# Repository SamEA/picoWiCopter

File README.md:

picoWiCopter
============

A small Quadcopter for multi robot cooperation

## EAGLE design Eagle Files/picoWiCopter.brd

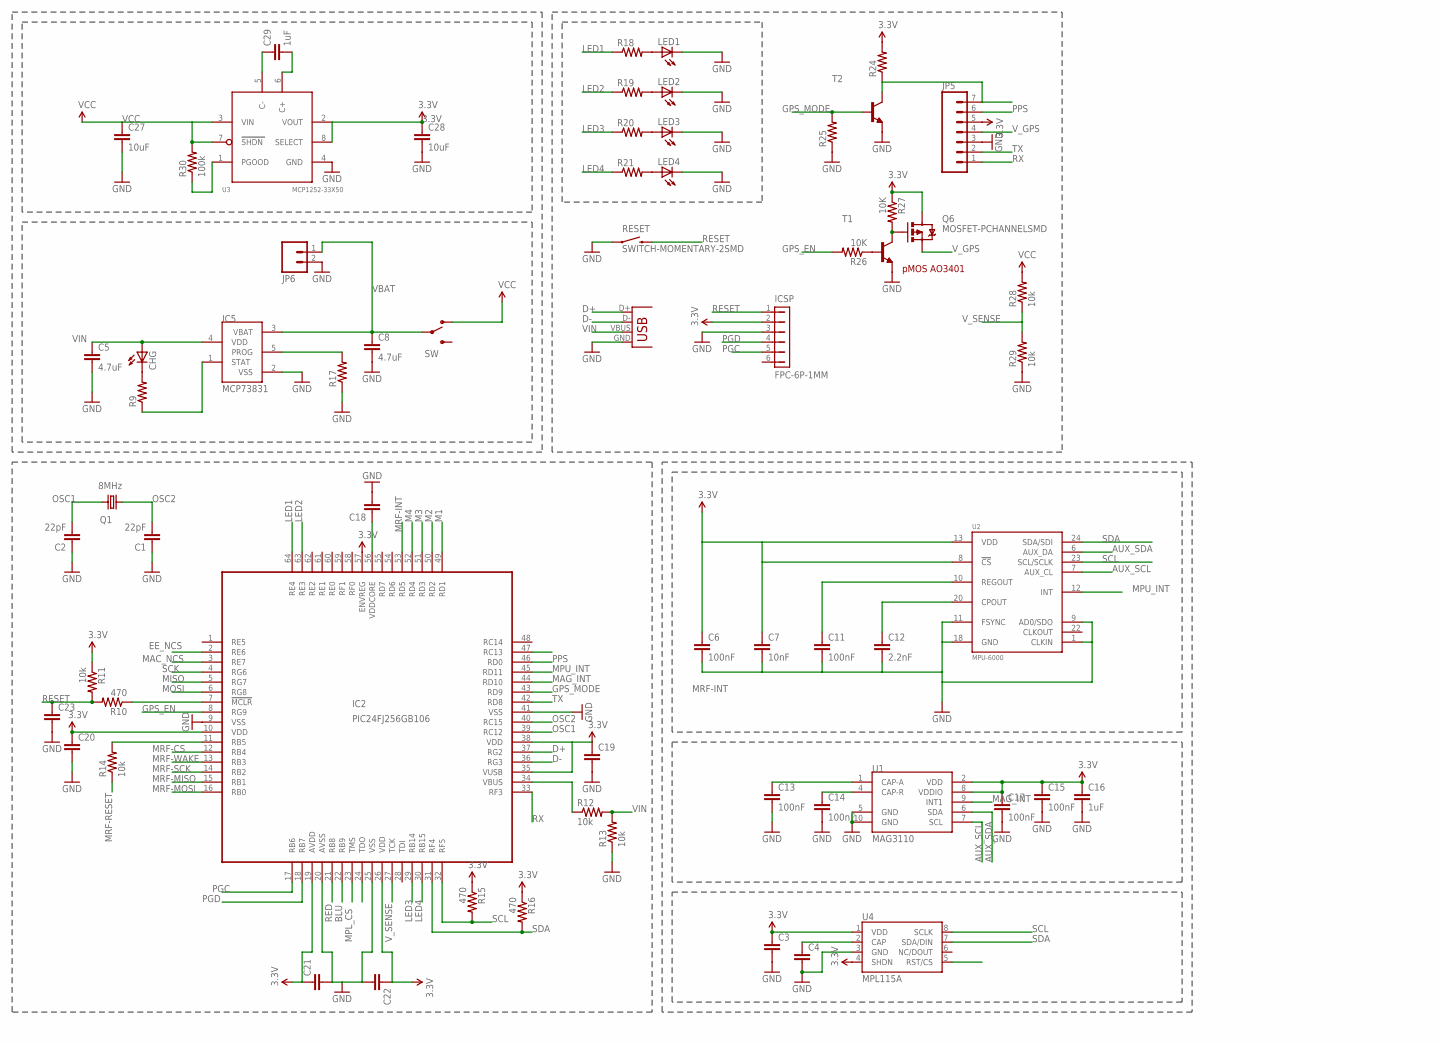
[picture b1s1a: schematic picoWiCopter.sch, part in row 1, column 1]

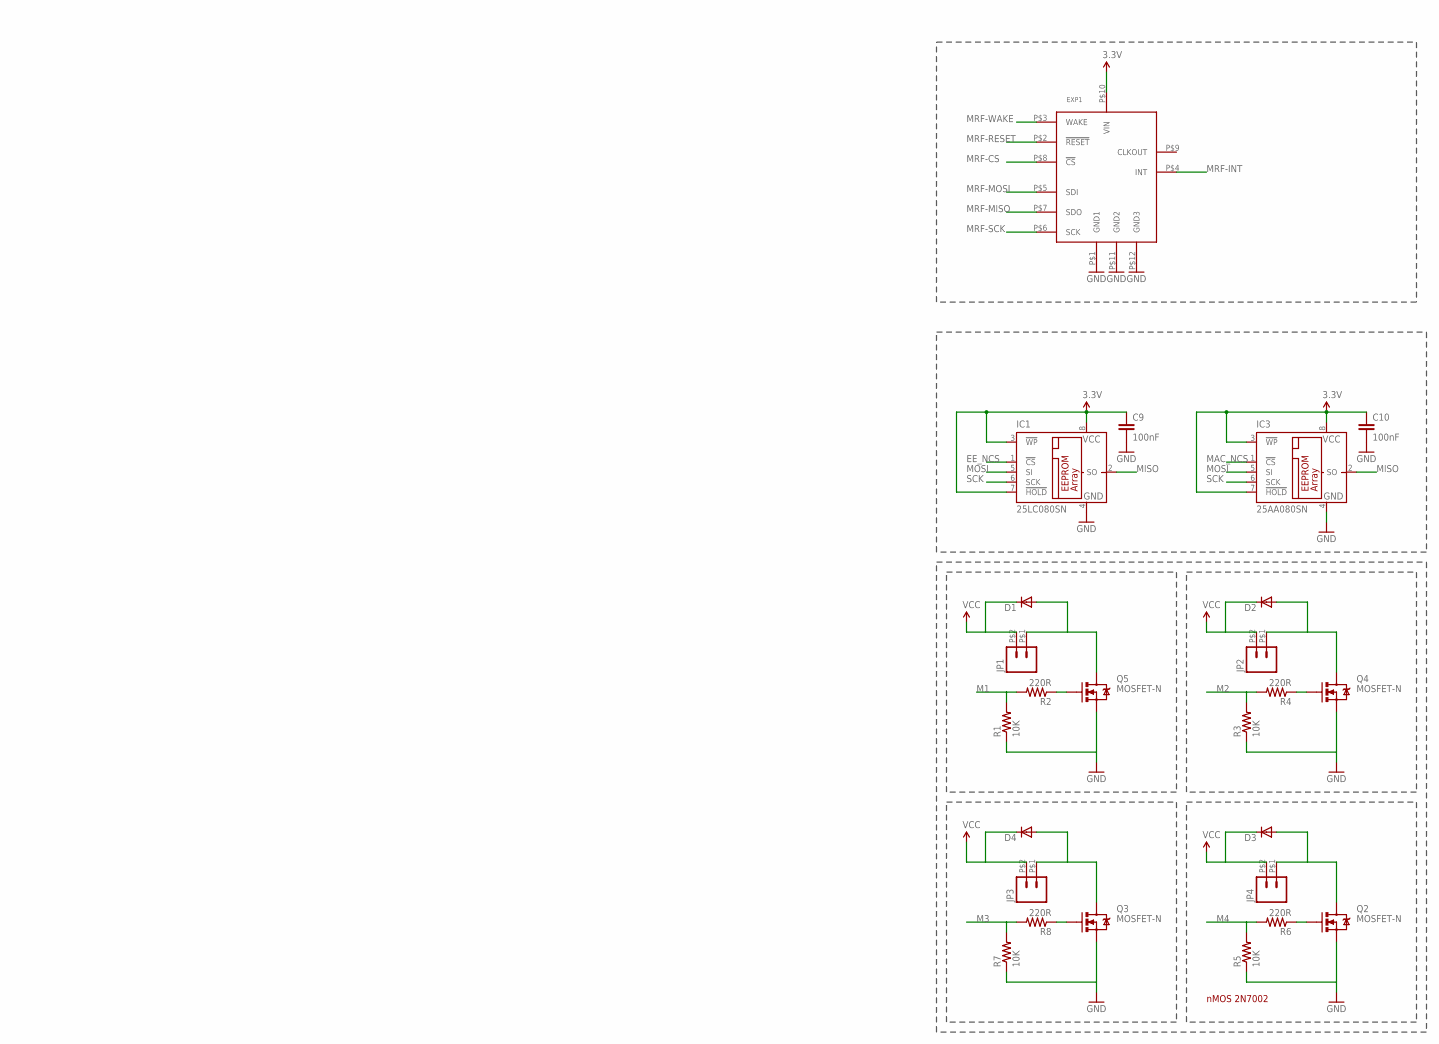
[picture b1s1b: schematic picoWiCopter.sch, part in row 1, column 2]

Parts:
C1, C2: 22pF; 0603-CAP
C3, C4, C19, C20, C21, C22, C23: CAP0603-CAP; 0603-CAP
C5, C8: 4.7uF; C1206
C6, C9, C10, C11, C13, C14, C15, C17: 100nF; 0603-CAP
C7: 10nF; 0603-CAP
C12: 2.2nF; 0603-CAP
C16, C29: 1uF; 0603-CAP
C18: CAP1206; 1206
C27, C28: 10uF; 1206
CHG: LEDCHIP-LED0603; CHIP-LED0603
D1, D2, D3, D4: DIODE-MINIMELF; MINIMELF
EXP1: MRF24J40MA"; MRF24J40MA
IC1: 25LC080SN; SO-08
IC2: PIC24FJ256GB106; TQFP64-10X10
IC3: 25AA080SN; SO-08
IC5: MCP73831; SOT23-5L
ICSP: FPC-6P-1MM
JP1, JP2, JP3, JP4: M02; 1X2SMD
JP5: M07; 1X07
JP6: M02PTH; 1X02
LED1, LED2, LED3, LED4: LED0603; LED-0603
Q1: 8MHz; CTS406
Q2, Q3, Q4, Q5: MOSFET-N; SOT23-3
Q6: MOSFET-PCHANNELSMD; SOT23-3
R1, R3, R5, R7, R26, R27: 10K; R0603
R2, R4, R6, R8: 220R; R0603
R9, R17, R18, R19, R20, R21, R24, R25: RESISTOR0603-RES; 0603-RES
R10, R15, R16: 470; 0603-RES
R11, R12, R13, R14, R28, R29: 10k; 0603-RES
R30: 100k; 0603-RES
RESET: SWITCH-MOMENTARY-2SMD; TACTILE_SWITCH_SMD
SW: SWITCH-SPDTPTH_LOCK; SWITCH-SPDT_LOCK.007S
T1, T2: BFR92-NPN-SOT23-BEC; SOT23-BEC
U1: MAG3110; DFN-10
U2: MPU-6000; QFN-24
U3: MCP1252-33X50; MSOP8
U4: MPL115A; LGA8
X3: USBSMD; USB-MINIB

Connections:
3.3V: C3.1, C6.1, C7.1, C9.1, C10.1, C15.1, C16.1, C17.1, C19.1, C20.1, C21.1, C22.1, C28.1, EXP1.P$10 (VIN), IC1.3 (!WP), IC1.7 (!HOLD), IC1.8 (VCC), IC2.10 (VDD), IC2.19 (AVDD), IC2.26 (VDD), IC2.35 (VUSB), IC2.38 (VDD), IC2.57 (ENVREG), IC3.3 (!WP), IC3.7 (!HOLD), IC3.8 (VCC), ICSP.2, JP5.5, Q6.3 (D), R11.1, R15.1, R16.1, R24.2, R27.1, U1.2 (VDD), U1.8 (VDDIO), U2.8 (!CS), U2.13 (VDD), U3.2 (VOUT), U3.8 (SELECT), U4.1 (VDD), U4.4 (SHDN)
AUX_SCL: U1.7 (SCL), U2.7 (AUX_CL)
AUX_SDA: U1.6 (SDA), U2.6 (AUX_DA)
BLU: IC2.22 (RB9)
C+1: C29.2, U3.6 (C+)
C-1: C29.1, U3.5 (C-)
D+: IC2.37 (RG2), X3.D+
D-: IC2.36 (RG3), X3.D-
EE_NCS: IC1.1 (!CS), IC2.2 (RE6)
GND: C1.1, C2.1, C3.2, C4.2, C5.2, C6.2, C7.2, C8.2, C9.2, C10.2, C11.2, C12.2, C13.2, C14.2, C15.2, C16.2, C17.2, C18.2, C19.2, C20.2, C21.2, C22.2, C23.2, C27.2, C28.2, EXP1.P$1 (GND1), EXP1.P$11 (GND2), EXP1.P$12 (GND3), IC1.4 (GND), IC2.9 (VSS), IC2.20 (AVSS), IC2.25 (VSS), IC2.41 (VSS), IC3.4 (GND), IC5.2 (VSS), ICSP.3, JP5.3, JP6.2, LED1.C, LED2.C, LED3.C, LED4.C, Q2.2 (S), Q3.2 (S), Q4.2 (S), Q5.2 (S), R1.1, R3.1, R5.1, R7.1, R13.1, R17.1, R25.1, R29.1, RESET.1, T1.E, T2.E, U1.5 (GND), U1.10 (GND), U2.1 (CLKIN), U2.9 (AD0/SDO), U2.11 (FSYNC), U2.18 (GND), U3.4 (GND), U4.3 (GND), X3.GND
GPS_EN: IC2.8 (RG9), R26.2
GPS_MODE: IC2.43 (RD9), R25.2, T2.B
LED1: IC2.64 (RE4), R18.1
LED2: IC2.63 (RE3), R19.1
LED3: IC2.29 (RB14), R20.1
LED4: IC2.30 (RB15), R21.1
M1: IC2.49 (RD1), R1.2, R2.2
M2: IC2.50 (RD2), R3.2, R4.2
M3: IC2.51 (RD3), R7.2, R8.2
M4: IC2.52 (RD4), R5.2, R6.2
MAC_NCS: IC2.3 (RE7), IC3.1 (!CS)
MAG_INT: IC2.44 (RD10), U1.9 (INT1)
MISO: IC1.2 (SO), IC2.5 (RG7), IC3.2 (SO)
MOSI: IC1.5 (SI), IC2.6 (RG8), IC3.5 (SI)
MPL_CS: IC2.23 (TMS), U4.5 (RST/CS)
MPU_INT: IC2.45 (RD11), U2.12 (INT)
MRF-CS: EXP1.P$8 (!CS), IC2.12 (RB4)
MRF-INT: EXP1.P$4 (INT), IC2.53 (RD5)
MRF-MISO: EXP1.P$7 (SDO), IC2.15 (RB1)
MRF-MOSI: EXP1.P$5 (SDI), IC2.16 (RB0)
MRF-RESET: EXP1.P$2 (!RESET), R14.1
MRF-SCK: EXP1.P$6 (SCK), IC2.14 (RB2)
MRF-WAKE: EXP1.P$3 (WAKE), IC2.13 (RB3)
unnamed: IC5.1 (STAT), R9.1
unnamed: CHG.C, R9.2
unnamed: C13.1, U1.1 (CAP-A)
unnamed: C14.1, U1.4 (CAP-R)
unnamed: D1.A, JP1.P$1 (1), Q5.3 (D)
unnamed: LED1.A, R18.2
unnamed: C18.1, IC2.56 (VDDCORE)
unnamed: IC2.34 (VBUS), R12.1
unnamed: IC2.7 (!MCLR), R10.1
unnamed: IC2.11 (RB5), R14.2
unnamed: D2.A, JP2.P$1 (1), Q4.3 (D)
unnamed: C12.1, U2.20 (CPOUT)
unnamed: C11.1, U2.10 (REGOUT)
unnamed: LED2.A, R19.2
unnamed: LED3.A, R20.2
unnamed: D3.A, JP4.P$1 (1), Q2.3 (D)
unnamed: LED4.A, R21.2
unnamed: D4.A, JP3.P$1 (1), Q3.3 (D)
unnamed: IC5.5 (PROG), R17.2
unnamed: JP5.7, R24.1, T2.C
unnamed: Q6.1 (G), R27.2, T1.C
unnamed: R26.1, T1.B
unnamed: R30.1, U3.1 (PGOOD)
unnamed: C4.1, U4.2 (CAP)
unnamed: Q5.1 (G), R2.1
unnamed: Q4.1 (G), R4.1
unnamed: Q2.1 (G), R6.1
unnamed: Q3.1 (G), R8.1
OSC1: C2.2, IC2.39 (RC12), Q1.3 (2)
OSC2: C1.2, IC2.40 (RC15), Q1.1
PGC: IC2.17 (RB6), ICSP.5
PGD: IC2.18 (RB7), ICSP.4
PPS: IC2.46 (RD0), JP5.6
RED: IC2.21 (RB8)
RESET: C23.1, ICSP.1, R10.2, R11.2, RESET.3 (2)
RX: IC2.33 (RF3), JP5.1
SCK: IC1.6 (SCK), IC2.4 (RG6), IC3.6 (SCK)
SCL: IC2.32 (RF5), R15.2, U2.23 (SCL/SCLK), U4.8 (SCLK)
SDA: IC2.31 (RF4), R16.2, U2.24 (SDA/SDI), U4.7 (SDA/DIN)
TX: IC2.42 (RD8), JP5.2
VBAT: C8.1, IC5.3 (VBAT), JP6.1, SW.2
VCC: C27.1, D1.C, D2.C, D3.C, D4.C, JP1.P$2 (2), JP2.P$2 (2), JP3.P$2 (2), JP4.P$2 (2), R28.2, R30.2, SW.1 (O), U3.3 (VIN), U3.7 (SHDN)
VIN: C5.1, CHG.A, IC5.4 (VDD), R12.2, R13.2, X3.VBUS
V_GPS: JP5.4, Q6.2 (S)
V_SENSE: IC2.27 (TCK), R28.1, R29.2

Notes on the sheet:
VBAT
nMOS 2N7002
pMOS AO3401

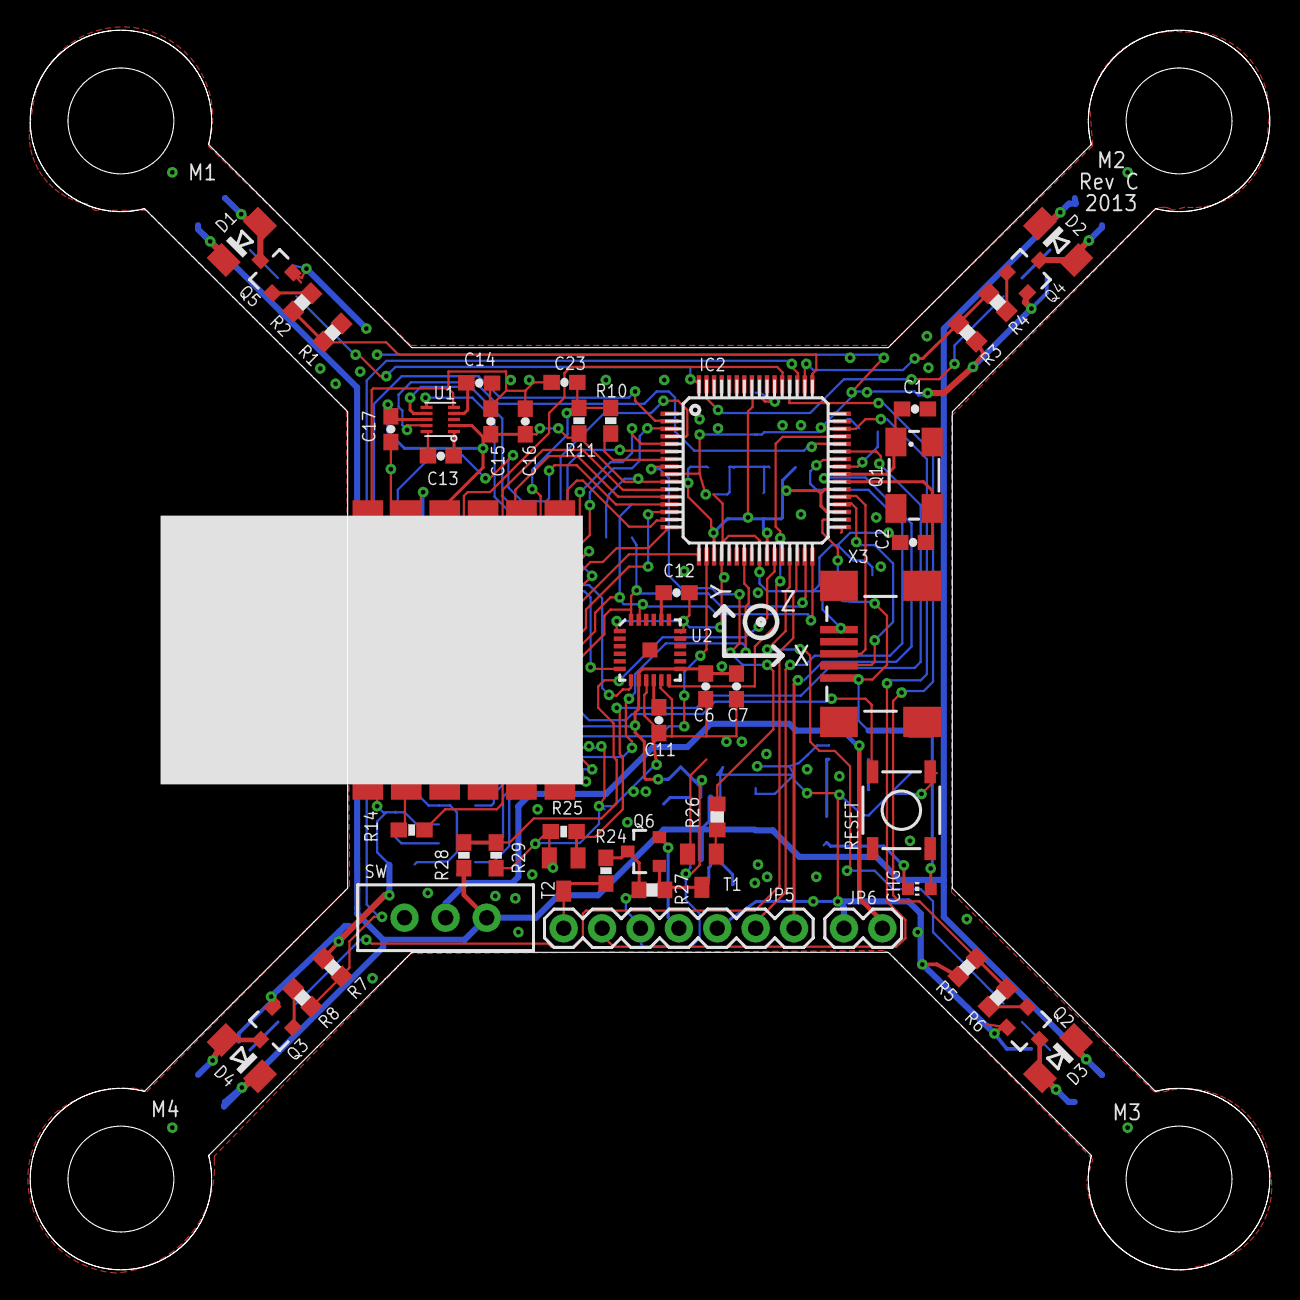
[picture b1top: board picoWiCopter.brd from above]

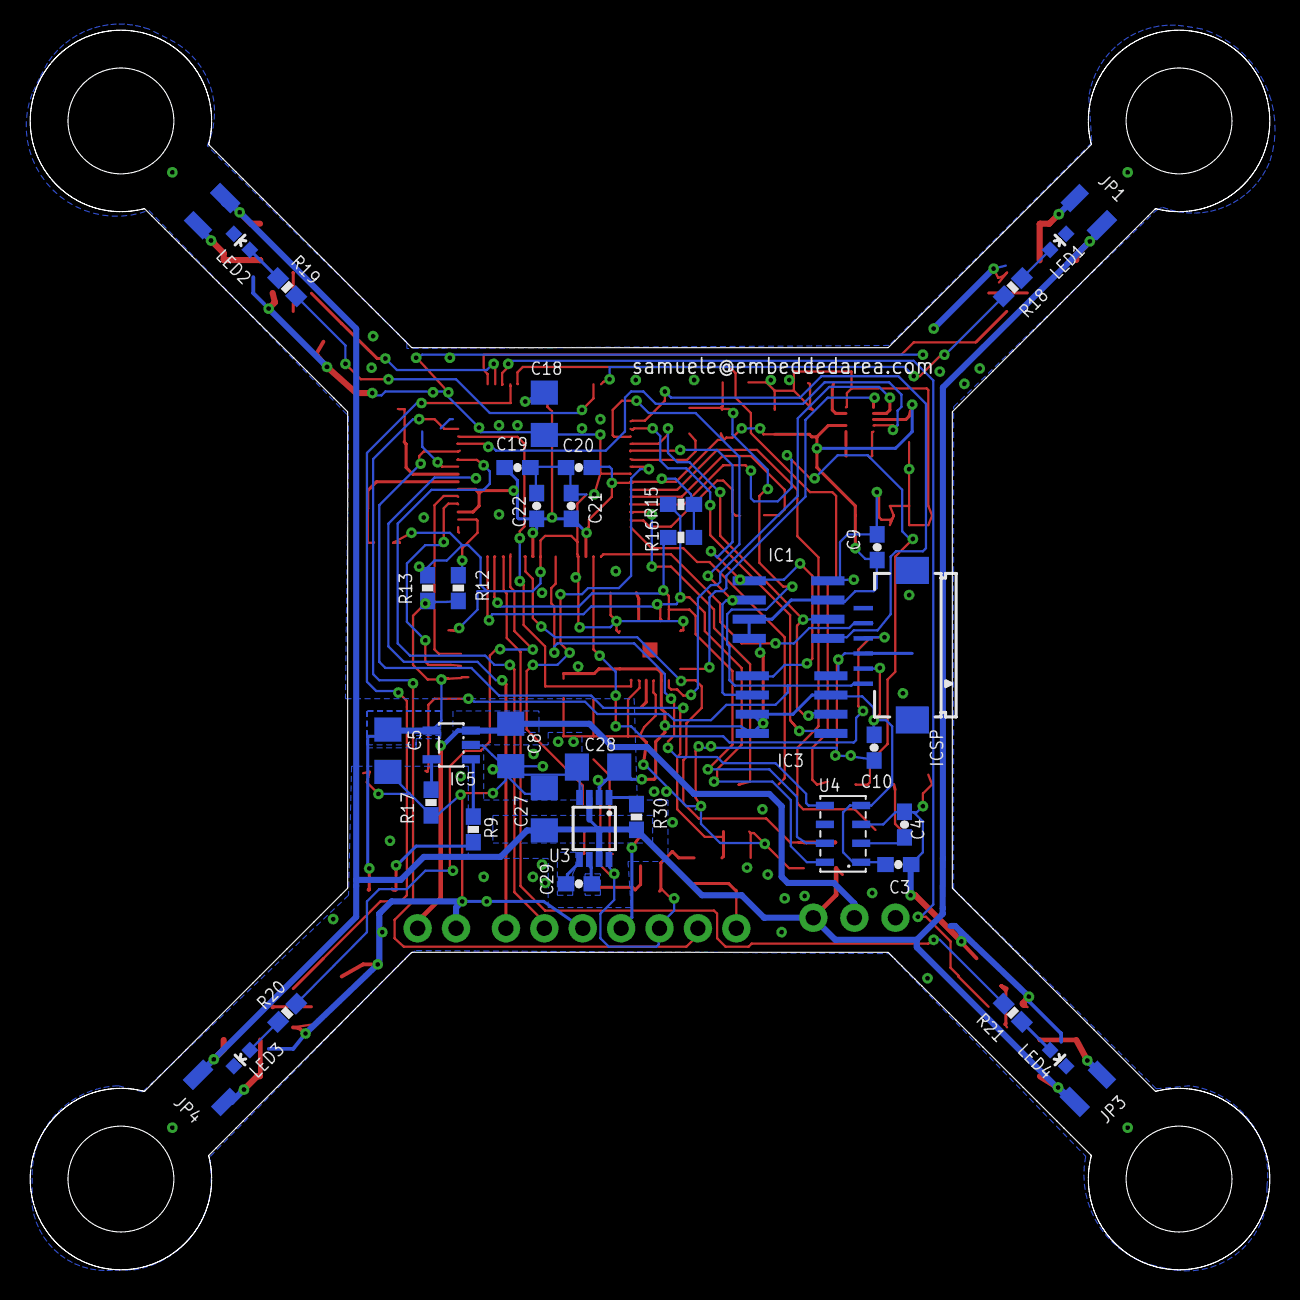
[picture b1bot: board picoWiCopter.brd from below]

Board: 2 copper layers, 82.0 x 82.0 mm, 90 parts (39 on the bottom side), 76 nets.

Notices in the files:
parts and their libraries:
SparkFun-Passives: Licensing: CC v3.0 Share-Alike You are welcome to use this library for commercial purposes.
